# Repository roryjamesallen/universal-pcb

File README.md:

# Universal PCB Project

### A Toadstool Tech - Allen Synthesis collaboration

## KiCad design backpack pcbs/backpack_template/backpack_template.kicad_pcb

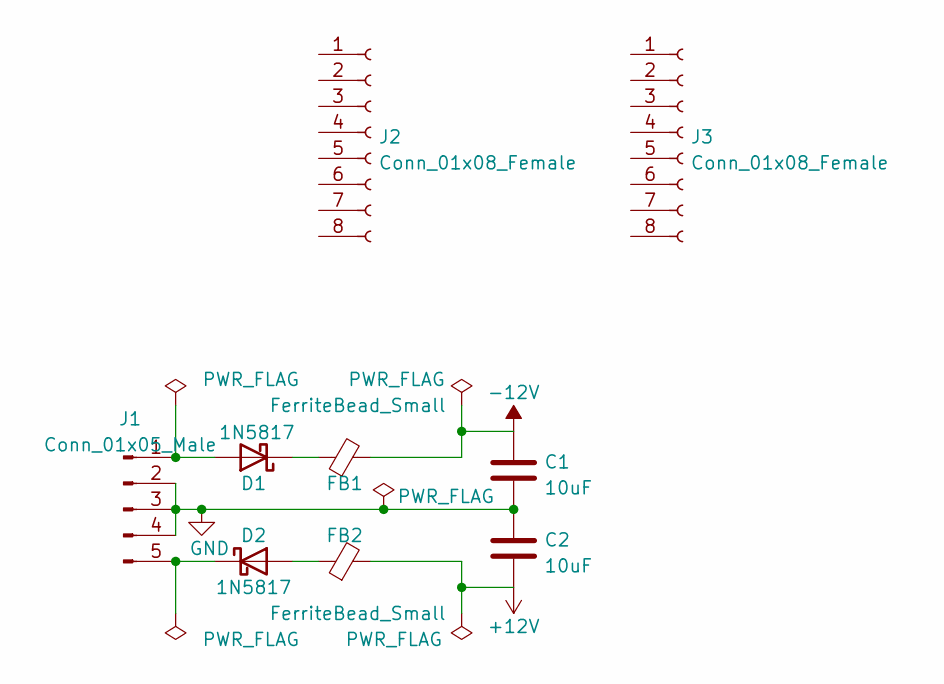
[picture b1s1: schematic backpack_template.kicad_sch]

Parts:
C1, C2: 10uF; C_0805_2012Metric
D1, D2: 1N5817; D_SOD-123
FB1, FB2: FerriteBead_Small; R_0603_1608Metric
J1: Conn_01x05_Male; PinHeader_1x05_P2.54mm_Vertical
J2, J3: Conn_01x08_Female; PinSocket_1x08_P2.54mm_Vertical

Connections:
+12V: C2.2, FB2.2
-12V: C1.1, FB1.2
GND: C1.2, C2.1, J1.2, J1.3, J1.4
unnamed: D1.1 (K), FB1.1
unnamed: D1.2 (A), J1.1
unnamed: D2.1 (K), J1.5
unnamed: D2.2 (A), FB2.1

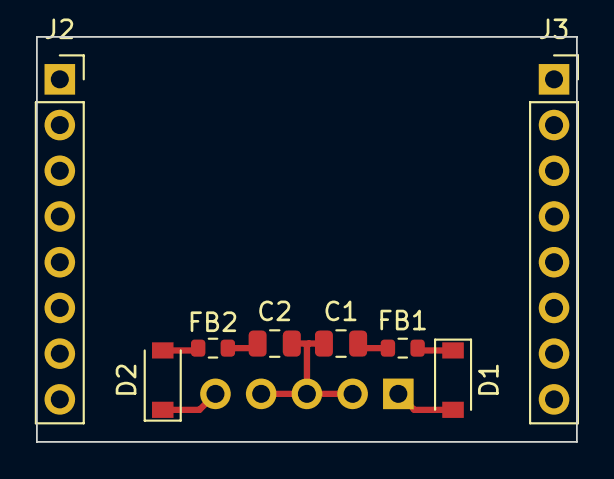
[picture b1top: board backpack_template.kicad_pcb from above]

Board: 2 copper layers, 30.0 x 22.5 mm, 9 parts (1 on the bottom side), 7 nets.

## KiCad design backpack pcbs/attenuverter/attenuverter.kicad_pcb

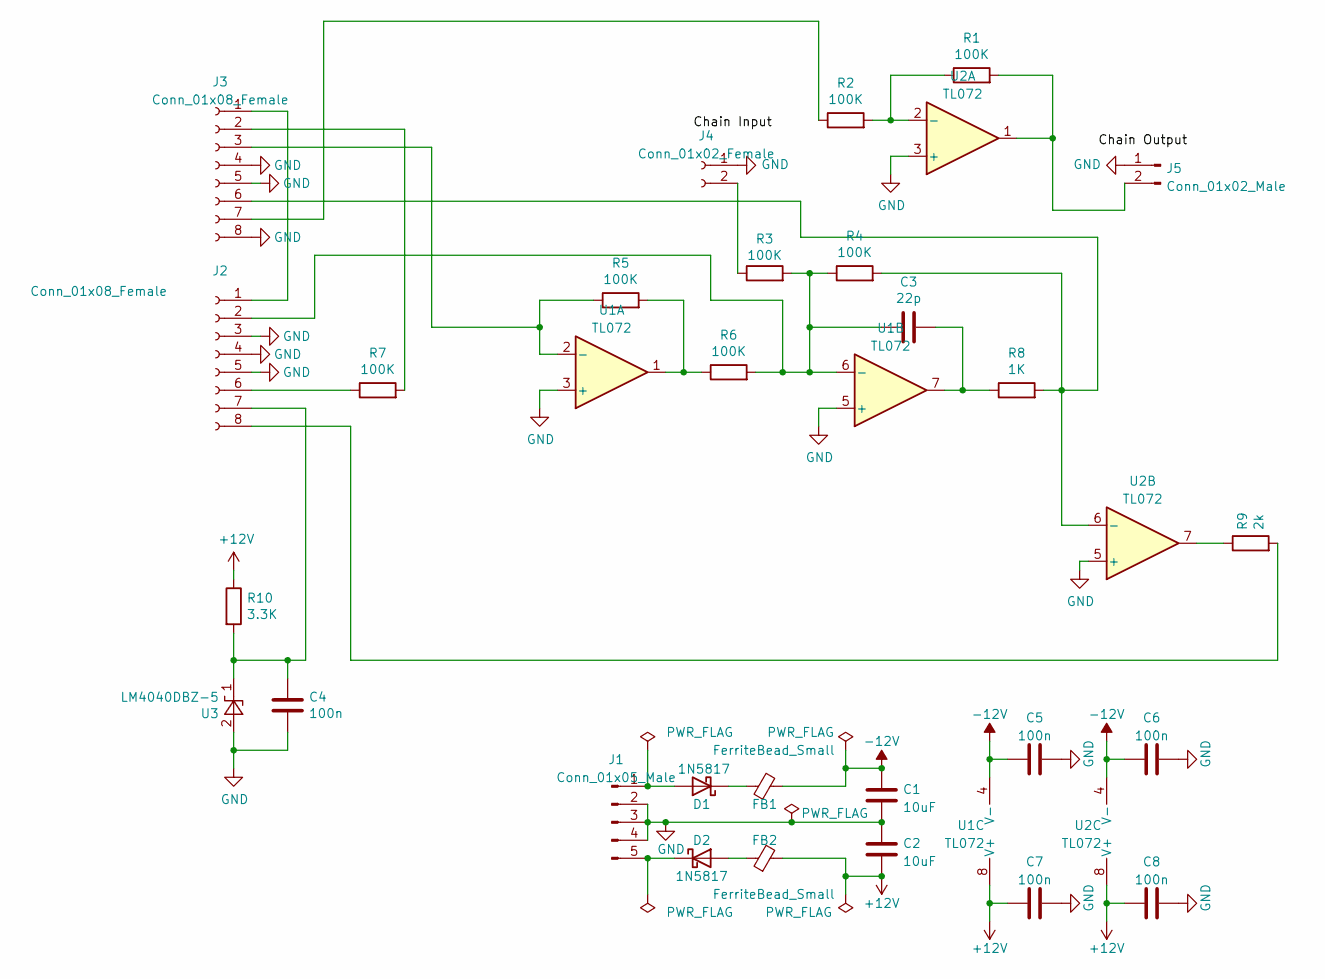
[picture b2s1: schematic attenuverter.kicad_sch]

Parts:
C1, C2: 10uF; C_0805_2012Metric
C3: 22p; C_0603_1608Metric
C4, C5, C6, C7, C8: 100n; C_0603_1608Metric
D1, D2: 1N5817; D_SOD-123
FB1, FB2: FerriteBead_Small; R_0603_1608Metric
J1: Conn_01x05_Male; PinHeader_1x05_P2.54mm_Vertical
J2, J3: Conn_01x08_Female; PinSocket_1x08_P2.54mm_Vertical
J4: Conn_01x02_Female; JST_EH_B2B-EH-A_1x02_P2.50mm_Vertical
J5: Conn_01x02_Male; JST_EH_B2B-EH-A_1x02_P2.50mm_Vertical
R1, R2, R3, R4, R5, R6, R7: 100K; R_0603_1608Metric
R8: 1K; R_0603_1608Metric
R9: 2k; R_0603_1608Metric
R10: 3.3K; R_0603_1608Metric
U1, U2: TL072; SOIC-8_3.9x4.9mm_P1.27mm
U3: LM4040DBZ-5; SOT-23

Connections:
+12V: C2.2, C7.1, C8.1, FB2.2, R10.1, U1.8 (V+), U2.8 (V+)
-12V: C1.1, C5.1, C6.1, FB1.2, U1.4 (V-), U2.4 (V-)
GND: C1.2, C2.1, C4.1, C5.2, C6.2, C7.2, C8.2, J1.2, J1.3, J1.4, J2.3, J2.4, J2.5, J3.4, J3.5, J3.8, J4.1, J5.1, U1.3 (+), U1.5 (+), U2.3 (+), U2.5 (+), U3.2 (A)
unnamed: C3.1, R8.1, U1.7
unnamed: D1.1 (K), FB1.1
unnamed: D1.2 (A), J1.1
unnamed: D2.1 (K), J1.5
unnamed: D2.2 (A), FB2.1
unnamed: J2.1, J3.1
unnamed: C3.2, J2.2, R3.2, R4.1, R6.2, U1.6 (-)
unnamed: J2.6, R7.1
unnamed: C4.2, J2.7, R10.2, U3.1 (K)
unnamed: J2.8, R9.2
unnamed: J3.2, R7.2
unnamed: J3.3, R5.1, U1.2 (-)
unnamed: J3.6, R4.2, R8.2, U2.6 (-)
unnamed: J3.7, R2.1
unnamed: J4.2, R3.1
unnamed: J5.2, R1.2, U2.1
unnamed: R1.1, R2.2, U2.2 (-)
unnamed: R5.2, R6.1, U1.1
unnamed: R9.1, U2.7

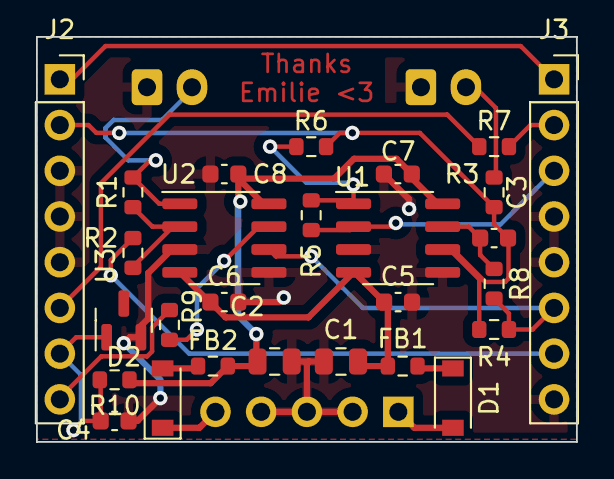
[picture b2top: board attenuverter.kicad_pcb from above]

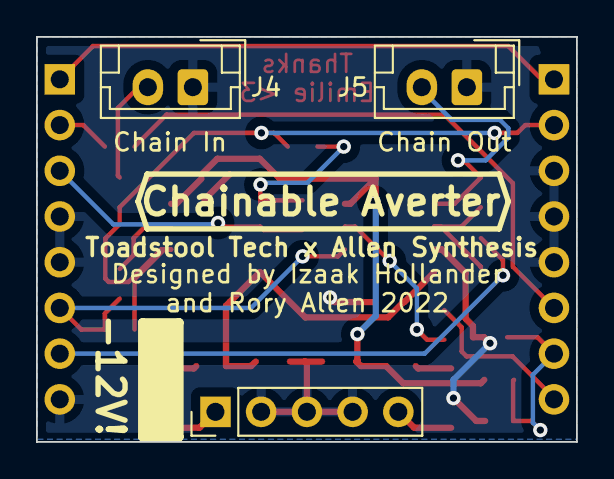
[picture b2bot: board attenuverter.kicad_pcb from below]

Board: 2 copper layers, 30.0 x 22.5 mm, 30 parts (3 on the bottom side), 22 nets.

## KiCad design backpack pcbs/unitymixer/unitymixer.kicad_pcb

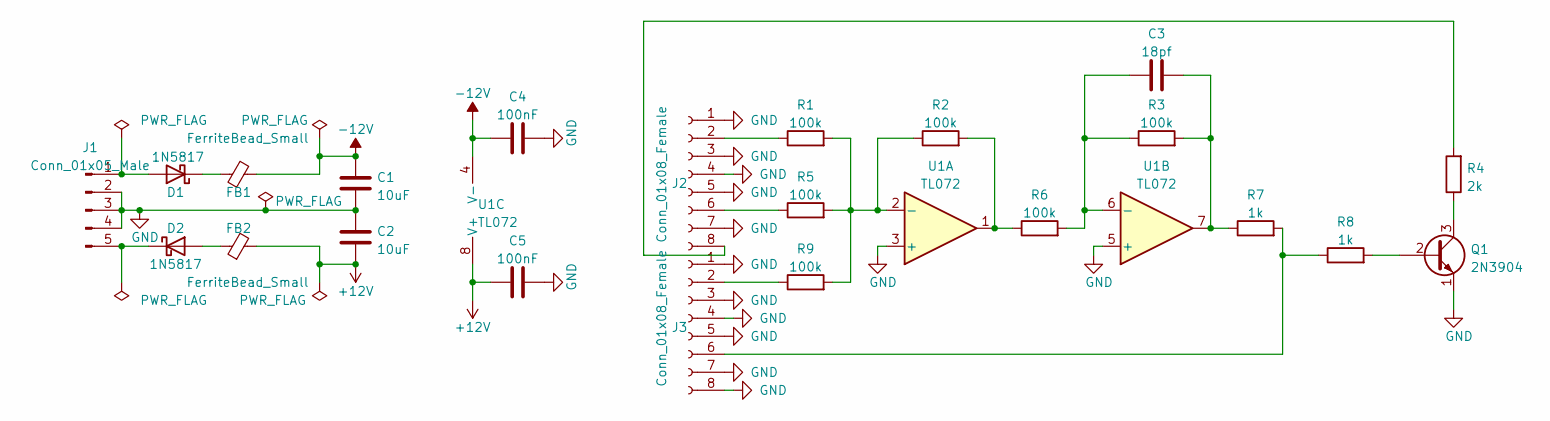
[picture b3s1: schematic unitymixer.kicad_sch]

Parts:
C1, C2: 10uF; C_0805_2012Metric
C3: 18pf; C_0603_1608Metric
C4, C5: 100nF; C_0603_1608Metric
D1, D2: 1N5817; D_SOD-123
FB1, FB2: FerriteBead_Small; R_0603_1608Metric
J1: Conn_01x05_Male; PinHeader_1x05_P2.54mm_Vertical
J2, J3: Conn_01x08_Female; PinSocket_1x08_P2.54mm_Vertical
Q1: 2N3904; SOT-23
R1, R2, R3, R5, R6, R9: 100k; R_0603_1608Metric
R4: 2k; R_0603_1608Metric
R7, R8: 1k; R_0603_1608Metric
U1: TL072; SOIC-8_3.9x4.9mm_P1.27mm

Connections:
+12V: C2.2, C5.1, FB2.2, U1.8 (V+)
-12V: C1.1, C4.1, FB1.2, U1.4 (V-)
GND: C1.2, C2.1, C4.2, C5.2, J1.2, J1.3, J1.4, J2.1, J2.3, J2.4, J2.5, J2.7, J3.1, J3.3, J3.4, J3.5, J3.7, J3.8, Q1.1 (E), U1.3 (+), U1.5 (+)
unnamed: C3.1, R3.1, R6.2, U1.6 (-)
unnamed: C3.2, R3.2, R7.1, U1.7
unnamed: D1.1 (K), FB1.1
unnamed: D1.2 (A), J1.1
unnamed: D2.1 (K), J1.5
unnamed: D2.2 (A), FB2.1
unnamed: J2.2, R1.1
unnamed: J2.6, R5.1
unnamed: J2.8, R4.2
unnamed: J3.2, R9.1
unnamed: J3.6, R7.2, R8.1
unnamed: Q1.2 (B), R8.2
unnamed: Q1.3 (C), R4.1
unnamed: R1.2, R2.1, R5.2, R9.2, U1.2 (-)
unnamed: R2.2, R6.1, U1.1

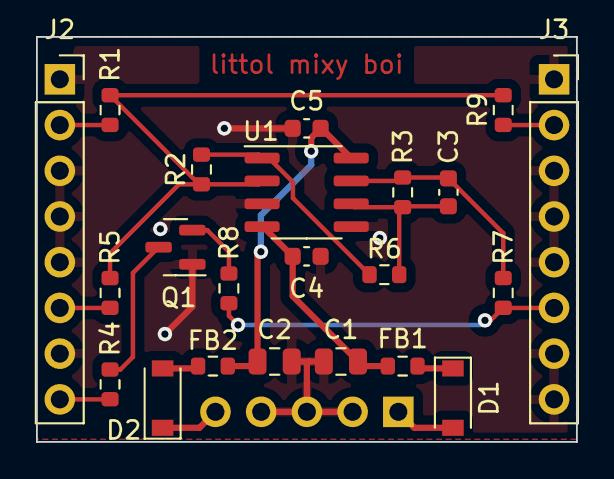
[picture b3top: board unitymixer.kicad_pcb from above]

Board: 2 copper layers, 30.0 x 22.5 mm, 23 parts (1 on the bottom side), 18 nets.

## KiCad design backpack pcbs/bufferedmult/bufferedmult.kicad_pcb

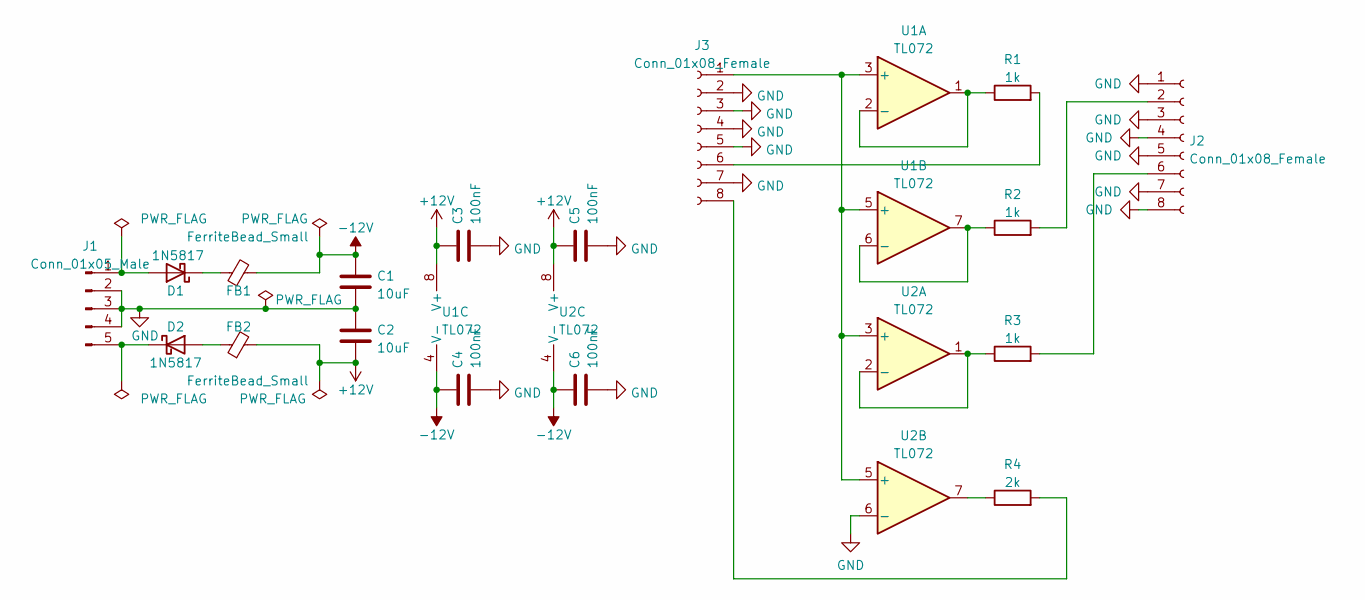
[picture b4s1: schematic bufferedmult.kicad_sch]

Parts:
C1, C2: 10uF; C_0805_2012Metric
C3, C4, C5, C6: 100nF; C_0603_1608Metric
D1, D2: 1N5817; D_SOD-123
FB1, FB2: FerriteBead_Small; R_0603_1608Metric
J1: Conn_01x05_Male; PinHeader_1x05_P2.54mm_Vertical
J2, J3: Conn_01x08_Female; PinSocket_1x08_P2.54mm_Vertical
R1, R2, R3: 1k; R_0603_1608Metric
R4: 2k; R_0603_1608Metric
U1, U2: TL072; SOIC-8_3.9x4.9mm_P1.27mm

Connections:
+12V: C2.2, C3.1, C5.1, FB2.2, U1.8 (V+), U2.8 (V+)
-12V: C1.1, C4.1, C6.1, FB1.2, U1.4 (V-), U2.4 (V-)
GND: C1.2, C2.1, C3.2, C4.2, C5.2, C6.2, J1.2, J1.3, J1.4, J2.1, J2.3, J2.4, J2.5, J2.7, J2.8, J3.2, J3.3, J3.4, J3.5, J3.7, U2.6 (-)
unnamed: D1.1 (K), FB1.1
unnamed: D1.2 (A), J1.1
unnamed: D2.1 (K), J1.5
unnamed: D2.2 (A), FB2.1
unnamed: J2.2, R2.2
unnamed: J2.6, R3.2
unnamed: J3.1, U1.3 (+), U1.5 (+), U2.3 (+), U2.5 (+)
unnamed: J3.6, R1.2
unnamed: J3.8, R4.2
unnamed: R1.1, U1.1, U1.2 (-)
unnamed: R2.1, U1.6 (-), U1.7
unnamed: R3.1, U2.1, U2.2 (-)
unnamed: R4.1, U2.7

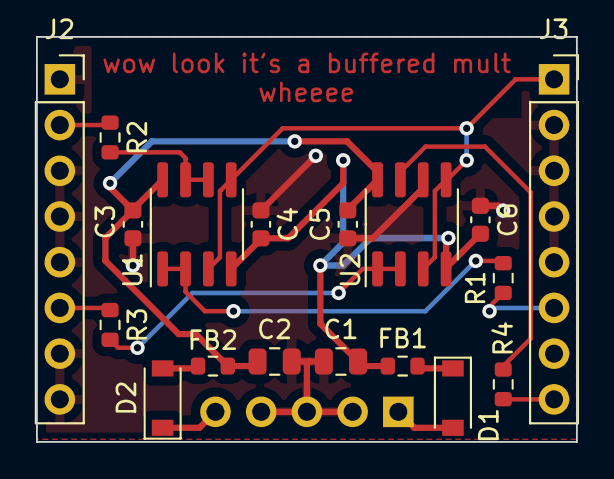
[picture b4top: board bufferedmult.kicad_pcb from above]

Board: 2 copper layers, 30.0 x 22.5 mm, 19 parts (1 on the bottom side), 16 nets.

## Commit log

2022-05-20 KiCad Changes
2022-05-23 Update README.md
    Added module ideas
2022-05-23 Update README.md
    Formatting
2022-05-23 KiCad Changes
    Added backpack pcbs and backpack_template. Also changed headers to 2.54mm (still needs some cleanup)
2022-05-24 KiCad Changes (2.54mm, cleaning up)
2022-05-24 File cleanup
2022-05-24 Backpack changes
2022-05-24 Add tactile switch footprints
2022-05-24 Backpack template PCB changes
2022-05-24 Add backpack template
2022-05-24 Added buffered mult
2022-05-24 create protoboard
2022-05-24 Added unitymixer
2022-05-24 Added attenuverter
2022-05-25 KiCad Save
2022-05-25 Create zip for template
2022-05-25 Save protoboard
2022-05-25 Add dimension for power header
2022-05-25 Re-create template zip
2022-05-25 Save template
2022-05-25 Create passive attenuator
2022-05-25 save
2022-07-09 create front panel for prototype, save kicad
2022-07-09 kicad save, add panel, add passive protoboard, gerbers
